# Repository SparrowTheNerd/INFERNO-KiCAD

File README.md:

# INFERNO-KiCAD
Ignition and Flow for Engine Regulation with Networked Operation

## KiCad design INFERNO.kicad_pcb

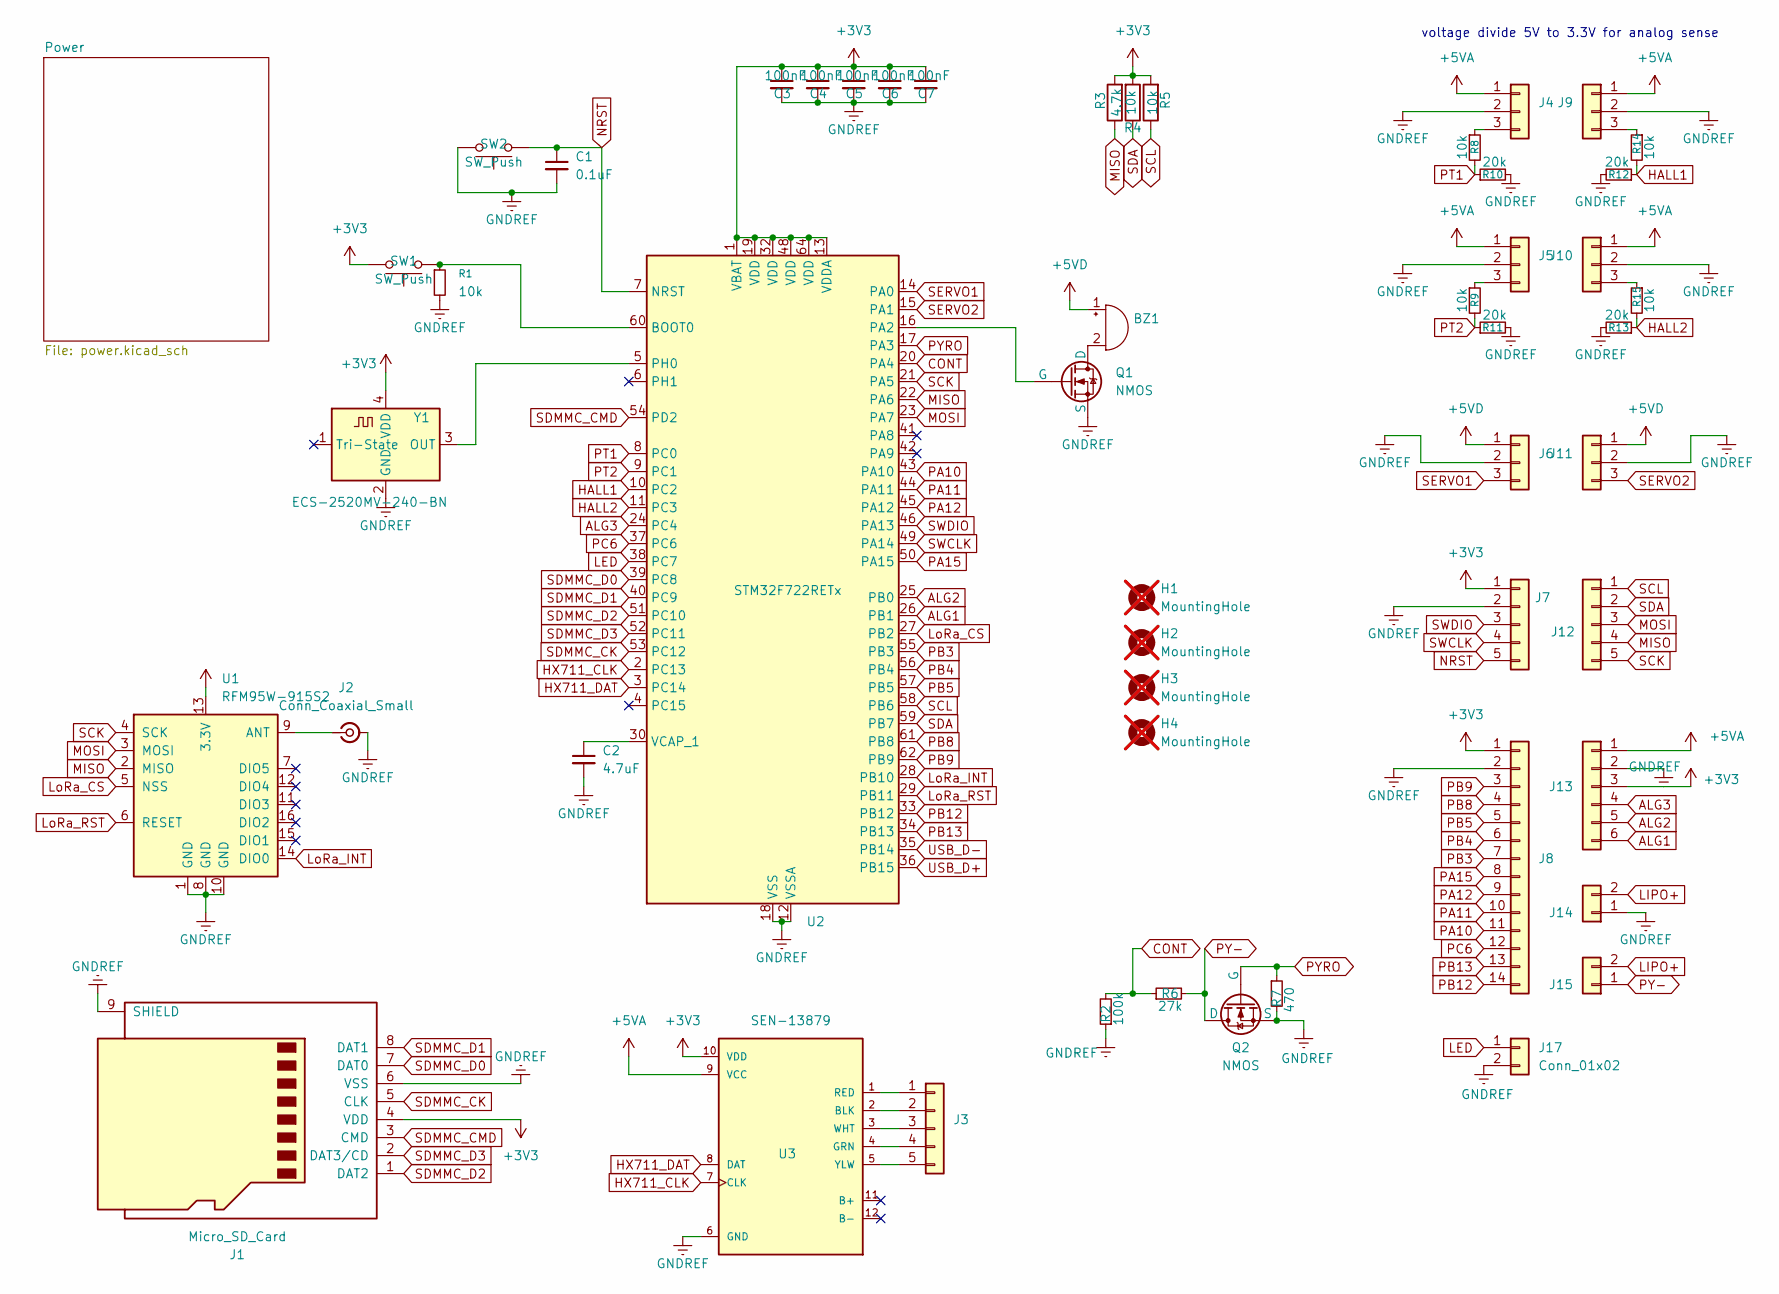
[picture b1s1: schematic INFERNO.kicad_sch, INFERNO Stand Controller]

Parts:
BZ1: CI12E-07T230-C-6; Buzzer_15x7.5RM7.6
C1: 0.1uF; C_0603_1608Metric
C2: 4.7uF; C_0603_1608Metric
C3, C4, C5, C6, C7: 100nF; C_0603_1608Metric; LCSC C1525
H1, H2, H3, H4: MountingHole; MountingHole_3.2mm_M3_ISO7380_Pad_TopBottom; not fitted
J1: Micro_SD_Card; microSD_HC_Molex_104031-0811
J2: Conn_Coaxial_Small; SMA_Molex_73251-1153_EdgeMount_Horizontal
J3: Conn_01x05; JST_XH_B5B-XH-AM_1x05_P2.50mm_Vertical
J4, J5, J9, J10: Conn_01x03; JST_XH_B3B-XH-A_1x03_P2.50mm_Vertical
J6, J11: Conn_01x03; PinSocket_1x03_P2.54mm_Vertical
J7, J12: Conn_01x05; PinHeader_1x05_P2.54mm_Vertical
J8: Conn_01x14; PinHeader_1x14_P2.54mm_Vertical
J13: Conn_01x06; PinHeader_1x06_P2.54mm_Vertical
J14: Conn_01x02; AMASS_XT30PW-M_1x02_P2.50mm_Horizontal
J15: Conn_01x02; TerminalBlock_Phoenix_MKDS-1,5-2-5.08_1x02_P5.08mm_Horizont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
J17: Conn_01x02; PinSocket_1x02_P2.54mm_Vertical
Q1: NMOS; SOT-323_SC-70
Q2: NMOS; TO-252-2
R1, R8, R9, R14, R15: 10k; R_0603_1608Metric
R2: 100k; R_0603_1608Metric; LCSC C25803
R3: 4.7k; R_0603_1608Metric; LCSC C23162
R4, R5: 10k; R_0603_1608Metric; LCSC C25804
R6: 27k; R_0603_1608Metric; LCSC C22967
R7: 470; R_0603_1608Metric; LCSC C23179
R10, R11, R12, R13: 20k; R_0603_1608Metric
SW1, SW2: SW_Push; SW_SPST_B3S-1000
U1: RFM95W-915S2; HOPERF_RFM9XW_SMD
U2: STM32F722RETx; LQFP-64_10x10mm_P0.5mm
U3: SEN-13879; SPARKFUN_SEN-13879
Y1: ECS-2520MV-240-BN; Oscillator_SMD_ECS_2520MV-xxx-xx-4Pin_2.5x2.0mm; LCSC C437141

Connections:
+3V3: C3.1, C4.1, C5.1, C6.1, C7.1, J1.4 (VDD), J7.1, J8.1, J13.3, R3.2, R4.2, R5.2, SW1.2, U1.13 (3.3V), U2.1 (VBAT), U2.13 (VDDA), U2.19 (VDD), U2.32 (VDD), U2.48 (VDD), U2.64 (VDD), U3.10 (VDD), Y1.4 (VDD); also elsewhere on the board
+5VA: J4.1, J5.1, J9.1, J10.1, J13.1, U3.9 (VCC); also elsewhere on the board
+5VD: BZ1.1 (+), J6.1, J11.1; also elsewhere on the board
ALG1: J13.6, U2.26 (PB1)
ALG2: J13.5, U2.25 (PB0)
ALG3: J13.4, U2.24 (PC4)
CONT: R2.2, R6.1, U2.20 (PA4)
GNDREF: C1.2, C2.2, C3.2, C4.2, C5.2, C6.2, C7.2, J1.6 (VSS), J1.9 (SHIELD), J2.2 (Ext), J4.2, J5.2, J6.2, J7.2, J8.2, J9.2, J10.2, J11.2, J13.2, J14.1, J17.2, Q1.3 (S), Q2.3 (S), R1.2, R2.1, R7.2, R10.2, R11.2, R12.2, R13.2, SW2.2, U1.1 (GND), U1.8 (GND), U1.10 (GND), U2.12 (VSSA), U2.18 (VSS), U2.31 (VSS), U2.47 (VSS), U2.63 (VSS), U3.6 (GND), Y1.2 (GND); also elsewhere on the board
HALL1: R12.1, R14.2, U2.10 (PC2)
HALL2: R13.1, R15.2, U2.11 (PC3)
HX711_CLK: U2.2 (PC13), U3.7 (CLK)
HX711_DAT: U2.3 (PC14), U3.8 (DAT)
LED: J17.1, U2.38 (PC7)
LIPO+: J14.2, J15.2; also elsewhere on the board
LoRa_CS: U1.5 (NSS), U2.27 (PB2)
LoRa_INT: U1.14 (DIO0), U2.28 (PB10)
LoRa_RST: U1.6 (RESET), U2.29 (PB11)
MISO: J12.4, R3.1, U1.2 (MISO), U2.22 (PA6)
MOSI: J12.3, U1.3 (MOSI), U2.23 (PA7)
NRST: C1.1, J7.5, SW2.1, U2.7 (NRST)
unnamed: BZ1.2 (-), Q1.1 (D)
unnamed: J2.1 (In), U1.9 (ANT)
unnamed: J3.1, U3.1 (RED)
unnamed: J3.2, U3.2 (BLK)
unnamed: J3.3, U3.3 (WHT)
unnamed: J3.4, U3.4 (GRN)
unnamed: J3.5, U3.5 (YLW)
unnamed: J4.3, R8.1
unnamed: J5.3, R9.1
unnamed: J9.3, R14.1
unnamed: J10.3, R15.1
unnamed: Q1.2 (G), U2.16 (PA2)
unnamed: R1.1, SW1.1, U2.60 (BOOT0)
unnamed: U2.5 (PH0), Y1.3 (OUT)
unnamed: C2.1, U2.30 (VCAP_1)
PA10: J8.11, U2.43 (PA10)
PA11: J8.10, U2.44 (PA11)
PA12: J8.9, U2.45 (PA12)
PA15: J8.8, U2.50 (PA15)
PB3: J8.7, U2.55 (PB3)
PB4: J8.6, U2.56 (PB4)
PB5: J8.5, U2.57 (PB5)
PB8: J8.4, U2.61 (PB8)
PB9: J8.3, U2.62 (PB9)
PB12: J8.14, U2.33 (PB12)
PB13: J8.13, U2.34 (PB13)
PC6: J8.12, U2.37 (PC6)
PT1: R8.2, R10.1, U2.8 (PC0)
PT2: R9.2, R11.1, U2.9 (PC1)
PY-: J15.1, Q2.2 (D), R6.2
PYRO: Q2.1 (G), R7.1, U2.17 (PA3)
SCK: J12.5, U1.4 (SCK), U2.21 (PA5)
SCL: J12.1, R5.1, U2.58 (PB6)
SDA: J12.2, R4.1, U2.59 (PB7)
SDMMC_CK: J1.5 (CLK), U2.53 (PC12)
SDMMC_CMD: J1.3 (CMD), U2.54 (PD2)
SDMMC_D0: J1.7 (DAT0), U2.39 (PC8)
SDMMC_D1: J1.8 (DAT1), U2.40 (PC9)
SDMMC_D2: J1.1 (DAT2), U2.51 (PC10)
SDMMC_D3: J1.2 (DAT3/CD), U2.52 (PC11)
SERVO1: J6.3, U2.14 (PA0)
SERVO2: J11.3, U2.15 (PA1)
SWCLK: J7.4, U2.49 (PA14)
SWDIO: J7.3, U2.46 (PA13)
USB_D+: U2.36 (PB15); also elsewhere on the board
USB_D-: U2.35 (PB14); also elsewhere on the board

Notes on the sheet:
voltage divide 5V to 3.3V for analog sense

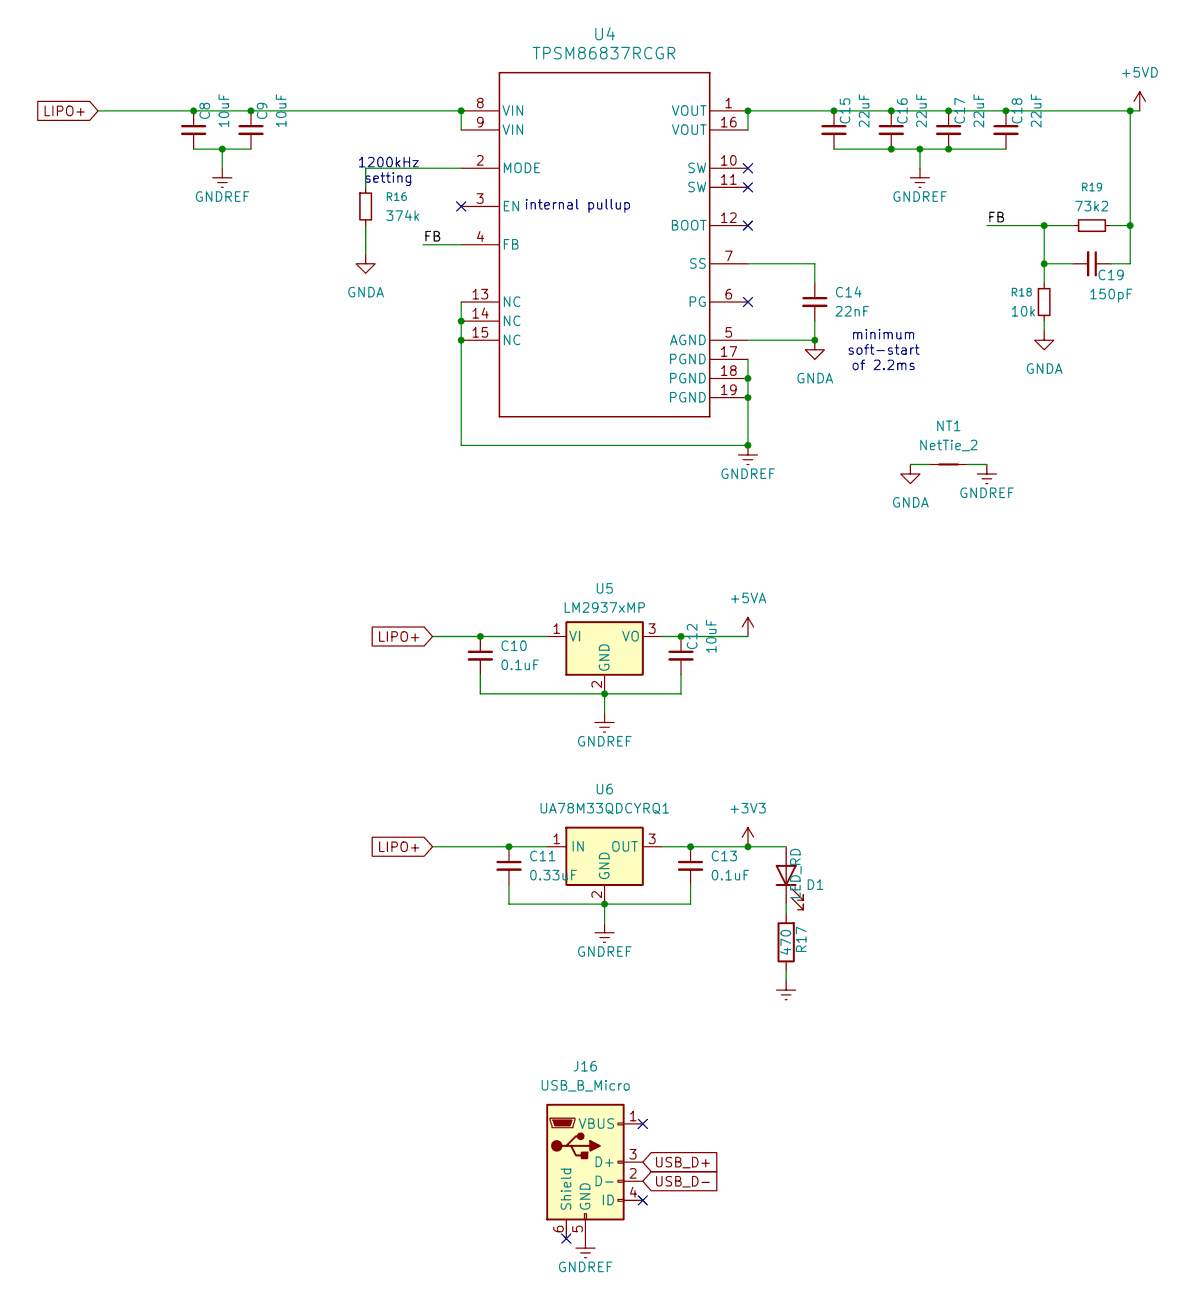
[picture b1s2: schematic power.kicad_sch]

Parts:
C8, C9, C12: 10uF; C_1206_3216Metric
C10, C13: 0.1uF; C_0603_1608Metric
C11: 0.33uF; C_0603_1608Metric
C14: 22nF; C_0603_1608Metric
C15, C16, C17, C18: 22uF; C_1210_3225Metric
C19: 150pF; C_0603_1608Metric
D1: LED_RD; LED_0603_1608Metric; LCSC C2286
J16: USB_B_Micro; USB_Micro-B_Amphenol_10118193-0001LF_Horizontal
NT1: NetTie_2
R16: 374k; R_0603_1608Metric
R17: 470; R_0603_1608Metric; LCSC C23179
R18: 10k; R_0603_1608Metric
R19: 73k2; R_0603_1608Metric
U4: TPSM86837RCGR; RCG0019A-MFG
U5: LM2937xMP; SOT-223-3_TabPin2
U6: UA78M33QDCYRQ1; SOT-223-3_TabPin2

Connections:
+3V3: C13.1, D1.2 (A), U6.3 (OUT); also elsewhere on the board
+5VA: C12.1, U5.3 (VO); also elsewhere on the board
+5VD: C15.1, C16.1, C17.1, C18.1, C19.1, R19.2, U4.1 (VOUT), U4.16 (VOUT); also elsewhere on the board
/Power/FB: C19.2, R18.1, R19.1, U4.4 (FB)
GNDA: C14.2, NT1.1, R16.2, R18.2, U4.5 (AGND)
GNDREF: C8.2, C9.2, C10.2, C11.2, C12.2, C13.2, C15.2, C16.2, C17.2, C18.2, J16.5 (GND), NT1.2, R17.1, U4.13 (NC), U4.14 (NC), U4.15 (NC), U4.17 (PGND), U4.18 (PGND), U4.19 (PGND), U5.2 (GND), U6.2 (GND); also elsewhere on the board
LIPO+: C8.1, C9.1, C10.1, C11.1, U4.8 (VIN), U4.9 (VIN), U5.1 (VI), U6.1 (IN); also elsewhere on the board
unnamed: D1.1 (K), R17.2
unnamed: R16.1, U4.2 (MODE)
unnamed: C14.1, U4.7 (SS)
USB_D+: J16.3 (D+); also elsewhere on the board
USB_D-: J16.2 (D-); also elsewhere on the board

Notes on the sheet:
minimum soft-start of 2.2ms
1200kHz setting
internal pullup

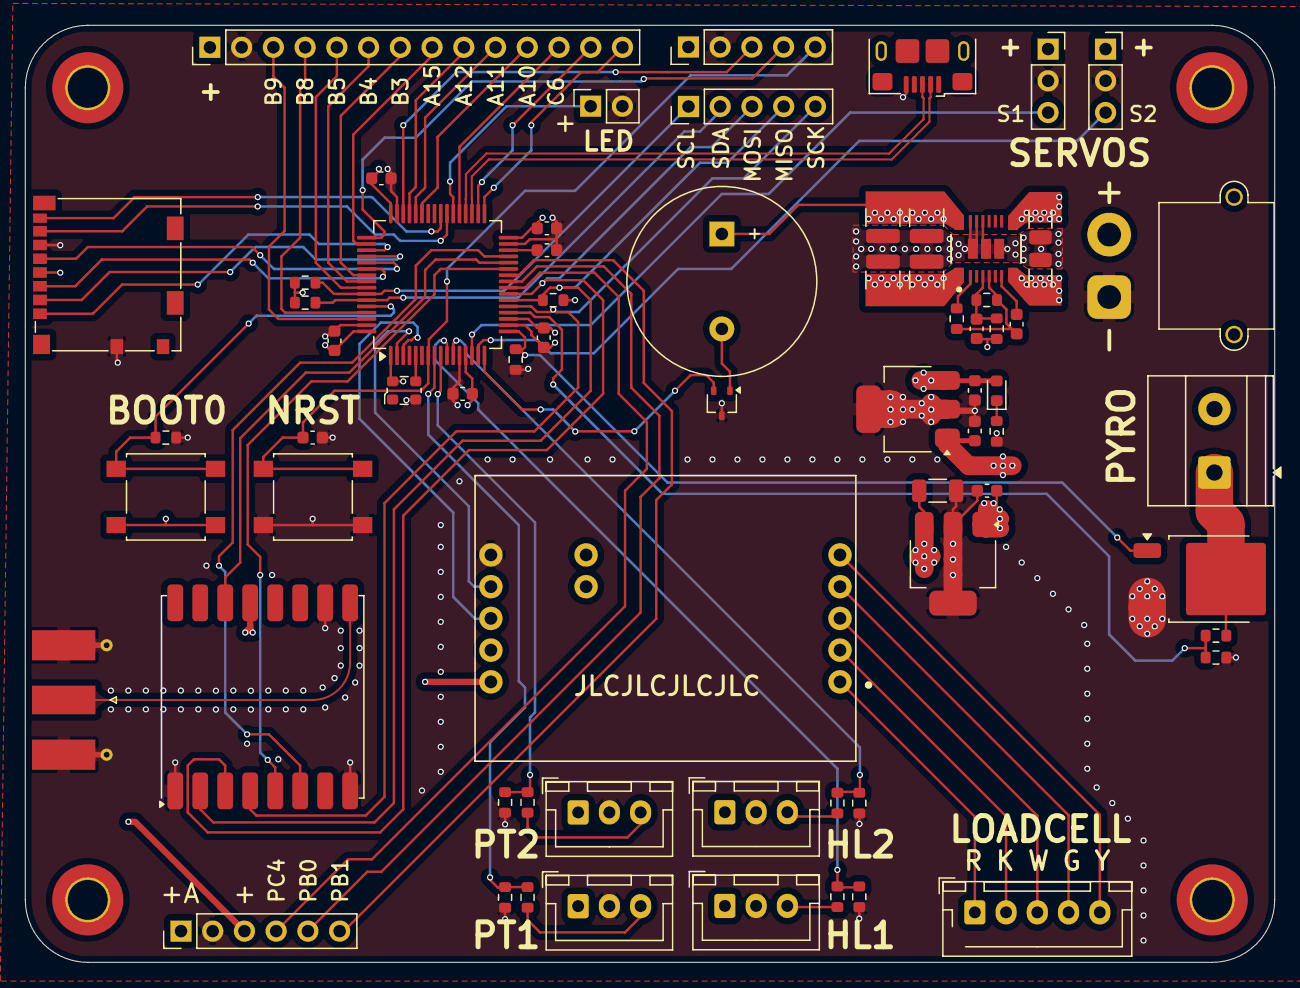
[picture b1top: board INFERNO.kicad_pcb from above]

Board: 4 copper layers, 100.0 x 75.0 mm, 72 parts (0 on the bottom side), 71 nets.

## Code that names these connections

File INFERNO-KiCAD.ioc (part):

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Mcu.Name=STM32F722R(C-E)Tx
Mcu.Package=LQFP64
Mcu.UserName=STM32F722RETx
PA0-WKUP.GPIOParameters=GPIO_Label
PA0-WKUP.GPIO_Label=SERVO1
PA0-WKUP.Signal=S_TIM2_CH1_ETR
PA1.GPIOParameters=GPIO_Label
PA1.GPIO_Label=SERVO2
PA1.Signal=S_TIM2_CH2
PA13.Mode=Serial_Wire
PA13.Signal=SYS_JTMS-SWDIO
PA14.Mode=Serial_Wire
PA14.Signal=SYS_JTCK-SWCLK
PA2.GPIOParameters=GPIO_Label
PA2.GPIO_Label=BUZZ
PA2.Signal=S_TIM2_CH3
PA3.GPIOParameters=GPIO_Label
PA3.GPIO_Label=PYRO
PA3.Signal=GPIO_Output
PA4.GPIOParameters=GPIO_Label
PA4.GPIO_Label=CONT
PA4.Signal=ADCx_IN4
PA5.Mode=Full_Duplex_Master
PA5.Signal=SPI1_SCK
PA6.Mode=Full_Duplex_Master
PA6.Signal=SPI1_MISO
PA7.Mode=Full_Duplex_Master
PA7.Signal=SPI1_MOSI
PB0.GPIOParameters=GPIO_Label
PB0.GPIO_Label=ALG2
PB0.Signal=ADCx_IN8
PB1.GPIOParameters=GPIO_Label
PB1.GPIO_Label=ALG1
PB1.Signal=ADCx_IN9
PB10.GPIOParameters=GPIO_Label
PB10.GPIO_Label=LoRa_INT
PB10.Signal=GPXTI10
PB11.GPIOParameters=GPIO_Label
PB11.GPIO_Label=LoRa_RST
PB11.Signal=GPIO_Output
PB14.GPIOParameters=GPIO_Label
PB14.GPIO_Label=USB_DM
PB14.Mode=Internal_Phy_Host
PB14.Signal=USB_OTG_HS_DM
PB15.GPIOParameters=GPIO_Label
PB15.GPIO_Label=USB_DP
PB15.Mode=Internal_Phy_Host
PB15.Signal=USB_OTG_HS_DP
PB2.GPIOParameters=GPIO_Label
PB2.GPIO_Label=LoRa_CS
PB2.Signal=GPIO_Output
PB6.Mode=I2C
PB6.Signal=I2C1_SCL
PB7.Mode=I2C
PB7.Signal=I2C1_SDA
PC0.GPIOParameters=GPIO_Label
PC0.GPIO_Label=PT1
PC0.Signal=ADCx_IN10
PC1.GPIOParameters=GPIO_Label
PC1.GPIO_Label=PT2
PC1.Signal=ADCx_IN11
PC10.Mode=SD_4_bits_Wide_bus
PC10.Signal=SDMMC1_D2
PC11.Mode=SD_4_bits_Wide_bus
PC11.Signal=SDMMC1_D3
PC12.Mode=SD_4_bits_Wide_bus
PC12.Signal=SDMMC1_CK
PC13.GPIOParameters=GPIO_Label
PC13.GPIO_Label=HX711_CLK
PC13.Signal=GPIO_Output
PC14-OSC32_IN.GPIOParameters=GPIO_Label
PC14-OSC32_IN.GPIO_Label=HX711_DAT
PC14-OSC32_IN.Signal=GPIO_Input
PC2.GPIOParameters=GPIO_Label
PC2.GPIO_Label=HALL1
PC2.Signal=ADCx_IN12
PC3.GPIOParameters=GPIO_Label
PC3.GPIO_Label=HALL2
PC3.Signal=ADCx_IN13
PC4.GPIOParameters=GPIO_Label
PC4.GPIO_Label=ALG3
PC4.Signal=ADCx_IN14
PC7.GPIOParameters=GPIO_Label
PC7.GPIO_Label=LED
PC7.Signal=GPIO_Output
PC8.Mode=SD_4_bits_Wide_bus
PC8.Signal=SDMMC1_D0
PC9.Mode=SD_4_bits_Wide_bus
PC9.Signal=SDMMC1_D1
PD2.Mode=SD_4_bits_Wide_bus
PD2.Signal=SDMMC1_CMD
PH0-OSC_IN.Mode=HSE-External-Clock-Source
PH0-OSC_IN.Signal=RCC_OSC_IN
PH1-OSC_OUT.Mode=HSE-External-Clock-Source
PH1-OSC_OUT.Signal=RCC_OSC_OUT
RCC.HSE_VALUE=24000000
RCC.SYSCLKFreq_VALUE=192000000
RCC.SYSCLKSource=RCC_SYSCLKSOURCE_PLLCLK
board=custom

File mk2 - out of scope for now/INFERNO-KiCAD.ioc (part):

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Mcu.Name=STM32H725VETx
Mcu.Package=LQFP100
Mcu.UserName=STM32H725VETx
PA0.GPIOParameters=GPIO_Label
PA0.GPIO_Label=PWM1
PA0.Signal=S_TIM2_CH1_ETR
PA1.GPIOParameters=GPIO_Label
PA1.GPIO_Label=PWM2
PA1.Signal=S_TIM2_CH2
PA11.Mode=Host_FS
PA11.Signal=USB_OTG_HS_DM
PA12.Mode=Host_FS
PA12.Signal=USB_OTG_HS_DP
PA13(JTMS/SWDIO).Mode=Serial_Wire
PA13(JTMS/SWDIO).Signal=DEBUG_JTMS-SWDIO
PA14(JTCK/SWCLK).Mode=Serial_Wire
PA14(JTCK/SWCLK).Signal=DEBUG_JTCK-SWCLK
PA2.GPIOParameters=GPIO_Label
PA2.GPIO_Label=PWM3
PA2.Signal=S_TIM2_CH3
PA3.GPIOParameters=GPIO_Label
PA3.GPIO_Label=PWM4
PA3.Signal=S_TIM2_CH4
PA4.GPIOParameters=GPIO_Label
PA4.GPIO_Label=PT1
PA4.Signal=ADCx_INP18
PA5.GPIOParameters=GPIO_Label
PA5.GPIO_Label=PT2
PA5.Signal=ADCx_INP19
PA6.GPIOParameters=GPIO_Label
PA6.GPIO_Label=PT3
PA6.Signal=ADCx_INP3
PA7.GPIOParameters=GPIO_Label
PA7.GPIO_Label=PT4
PA7.Signal=ADCx_INP7
PA8.Mode=Clock-out-1
PA8.Signal=RCC_MCO_1
PB0.GPIOParameters=GPIO_Label
PB0.GPIO_Label=ALG3
PB0.Signal=ADCx_INP9
PB1.GPIOParameters=GPIO_Label
PB1.GPIO_Label=ALG4
PB1.Signal=ADCx_INP5
PB13.Mode=Full_Duplex_Master
PB13.Signal=SPI2_SCK
PB14.Mode=Full_Duplex_Master
PB14.Signal=SPI2_MISO
PB15.Mode=Full_Duplex_Master
PB15.Signal=SPI2_MOSI
PB3(JTDO/TRACESWO).Mode=Full_Duplex_Master
PB3(JTDO/TRACESWO).Signal=SPI3_SCK
PB4(NJTRST).Mode=Full_Duplex_Master
PB4(NJTRST).Signal=SPI3_MISO
PB5.Mode=Full_Duplex_Master
PB5.Signal=SPI3_MOSI
PB6.Mode=I2C
PB6.Signal=I2C1_SCL
PB7.Mode=I2C
PB7.Signal=I2C1_SDA
PB8.GPIOParameters=GPIO_Label
PB8.GPIO_Label=SOL1
PB8.Signal=GPIO_Output
PB9.GPIOParameters=GPIO_Label
PB9.GPIO_Label=SOL2
PB9.Signal=GPIO_Output
PC10.Mode=SD_4_bits_Wide_bus
PC10.Signal=SDMMC1_D2
PC11.Mode=SD_4_bits_Wide_bus
PC11.Signal=SDMMC1_D3
PC12.Mode=SD_4_bits_Wide_bus
PC12.Signal=SDMMC1_CK
PC13.GPIOParameters=GPIO_Label
PC13.GPIO_Label=SOL6
PC13.Signal=GPIO_Output
PC14-OSC32_IN.GPIOParameters=GPIO_Label
PC14-OSC32_IN.GPIO_Label=SOL7
PC14-OSC32_IN.Signal=GPIO_Output
PC15-OSC32_OUT.GPIOParameters=GPIO_Label
PC15-OSC32_OUT.GPIO_Label=SOL8
PC15-OSC32_OUT.Signal=GPIO_Output
PC4.GPIOParameters=GPIO_Label
PC4.GPIO_Label=ALG1
PC4.Signal=ADCx_INP4
PC5.GPIOParameters=GPIO_Label
PC5.GPIO_Label=ALG2
PC5.Signal=ADCx_INP8
PC8.Mode=SD_4_bits_Wide_bus
PC8.Signal=SDMMC1_D0
PC9.Mode=SD_4_bits_Wide_bus
PC9.Signal=SDMMC1_D1
PD12.GPIOParameters=GPIO_Label
PD12.GPIO_Label=PWM5
PD12.Signal=S_TIM4_CH1
PD13.GPIOParameters=GPIO_Label
PD13.GPIO_Label=PWM6
PD13.Signal=S_TIM4_CH2
PD14.GPIOParameters=GPIO_Label
PD14.GPIO_Label=PWM7
PD14.Signal=S_TIM4_CH3
PD15.GPIOParameters=GPIO_Label
PD15.GPIO_Label=PWM8
PD15.Signal=S_TIM4_CH4
PD2.Mode=SD_4_bits_Wide_bus
PD2.Signal=SDMMC1_CMD
PE2.GPIOParameters=GPIO_Label
PE2.GPIO_Label=SOL3
PE2.Signal=GPIO_Output
PE4.GPIOParameters=GPIO_Label
PE4.GPIO_Label=SOL4
PE4.Signal=GPIO_Output
PE5.GPIOParameters=GPIO_Label
PE5.GPIO_Label=SOL5
PE5.Signal=GPIO_Output
PH0-OSC_IN.Mode=HSE-External-Clock-Source
PH0-OSC_IN.Signal=RCC_OSC_IN
RCC.HSE_VALUE=24000000
RCC.SYSCLKFreq_VALUE=240000000
RCC.SYSCLKSource=RCC_SYSCLKSOURCE_PLLCLK
board=custom

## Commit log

2025-10-14 uC pinouts, SD card, LoRa, load cell, and 5V digital and analog power circuitry
2025-10-17 finished mk1 design for production
